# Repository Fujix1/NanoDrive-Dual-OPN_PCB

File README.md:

# NanoDrive-Dual-OPN_PCB
PCB of NanoDrive Dual OPN for KiCad 7.

<br />この 作品 は <a rel="license" href="http://creativecommons.org/licenses/by-nc-sa/4.0/">クリエイティブ・コモンズ 表示 - 非営利 - 継承 4.0 国際 ライセンス</a>の下に提供されています。

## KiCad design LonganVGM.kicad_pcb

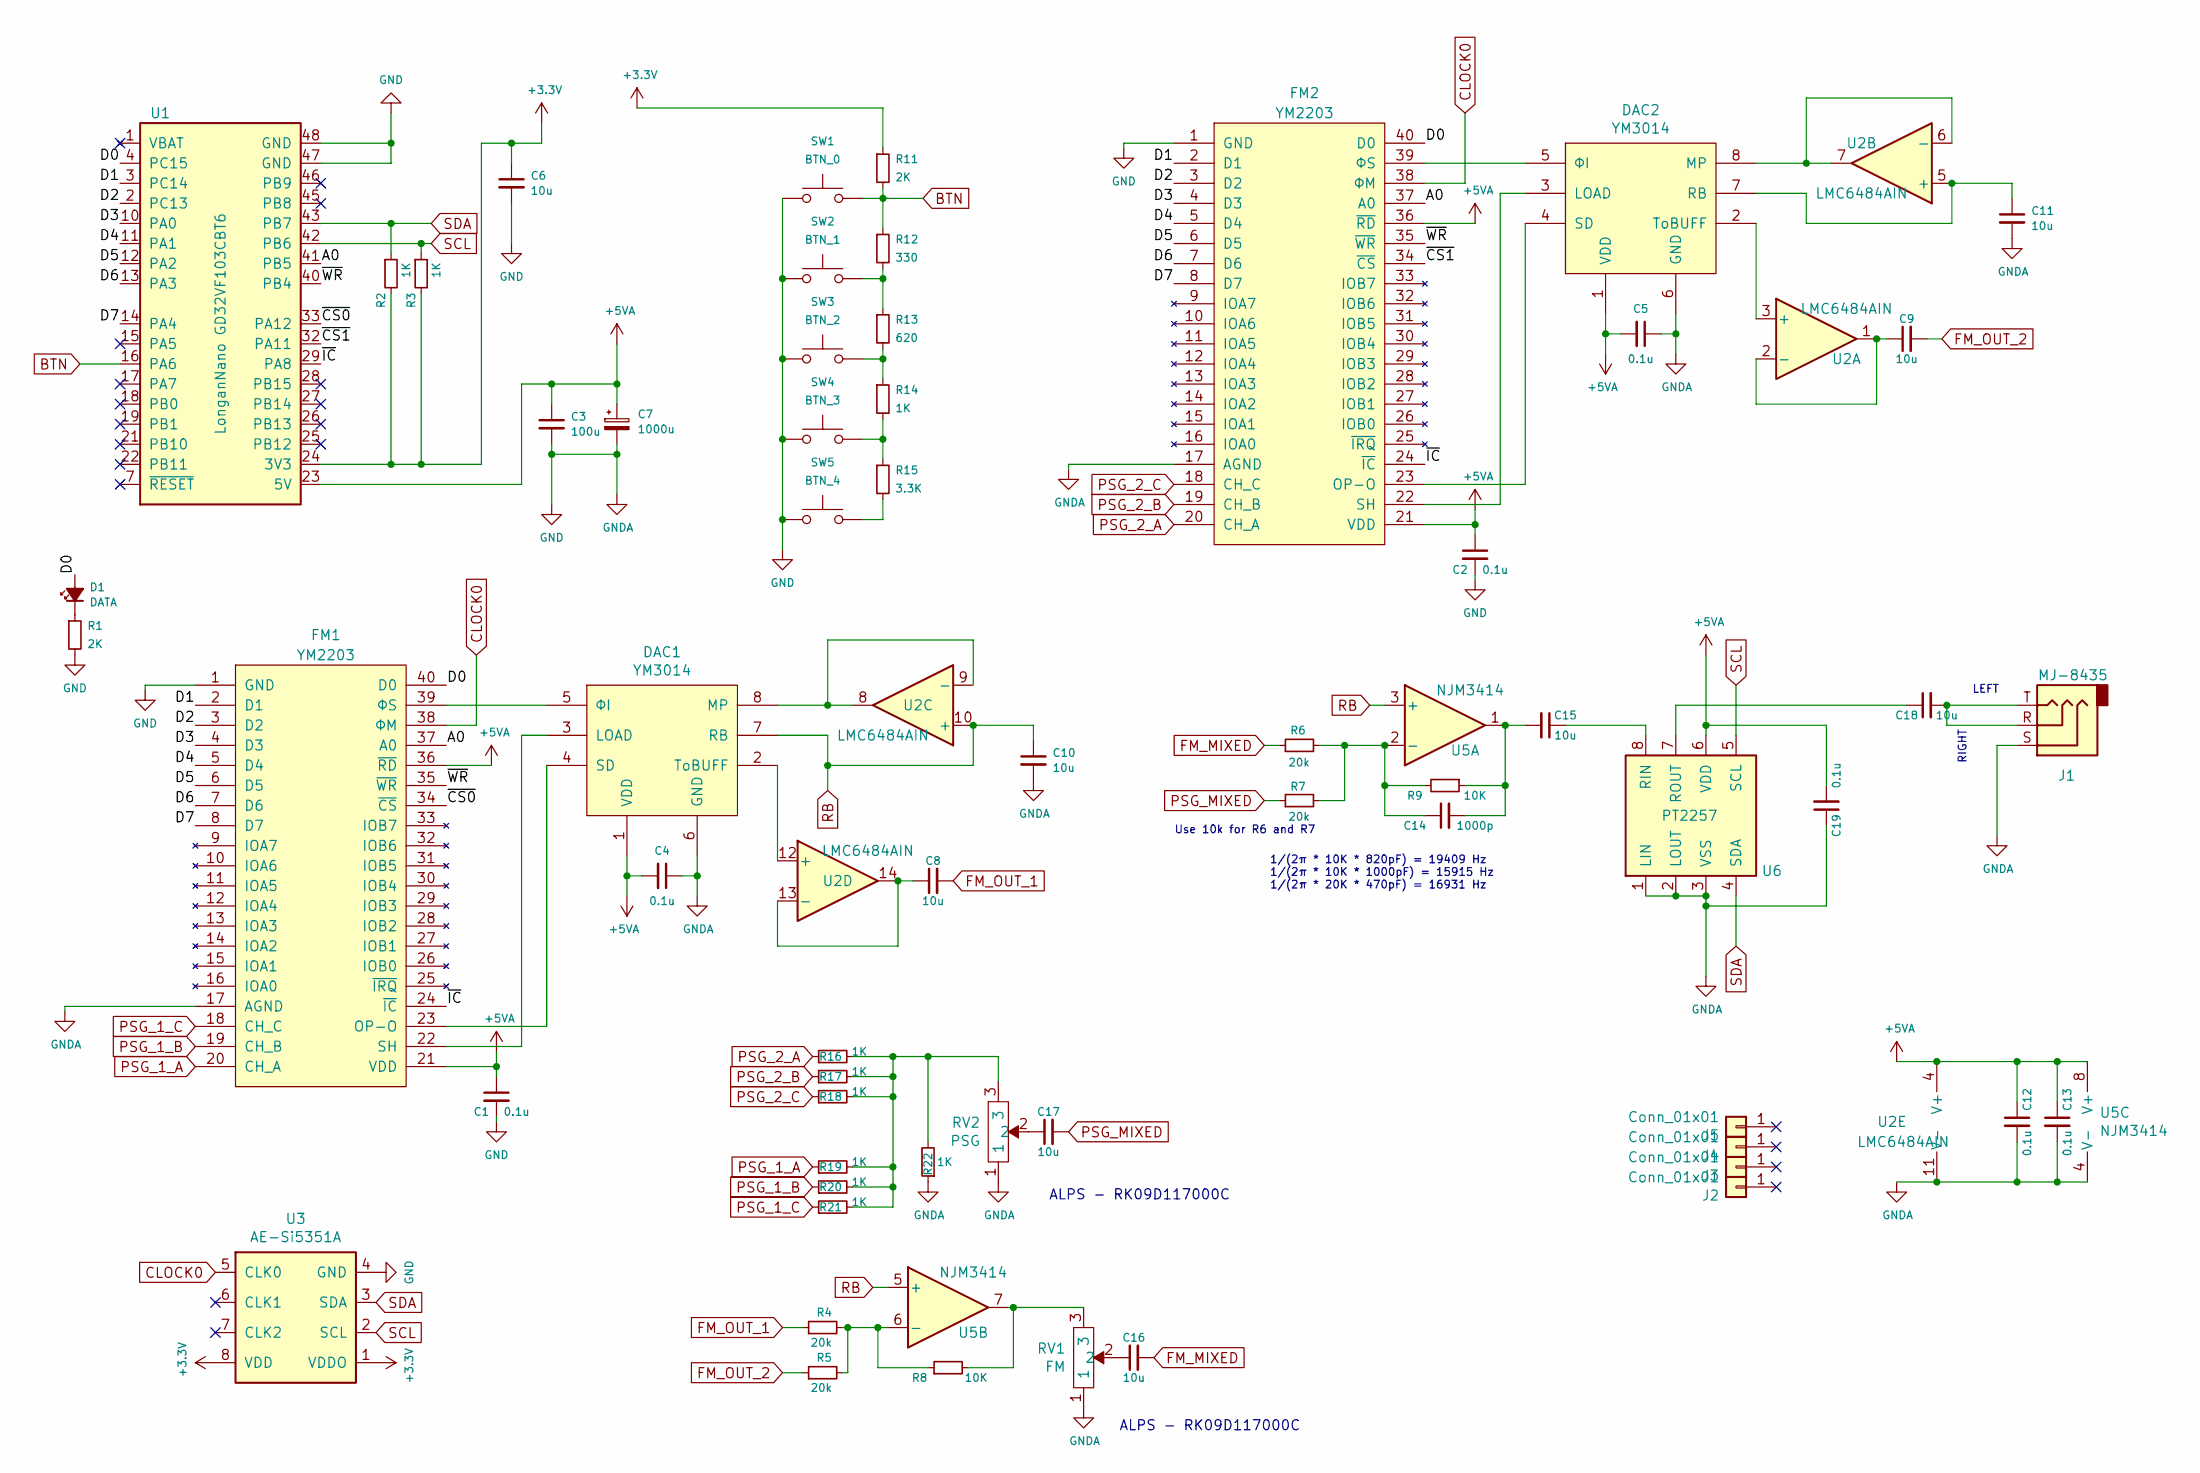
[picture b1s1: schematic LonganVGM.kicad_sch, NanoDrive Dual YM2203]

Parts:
C1, C2, C4, C5, C12, C13, C19: 0.1u; C_Disc_D4.3mm_W1.9mm_P5.00mm
C3: 100u; CP_Radial_D6.3mm_P2.50mm
C6, C8, C9, C10, C11, C15, C16, C17, C18: 10u; CP_Radial_D5.0mm_P2.00mm
C7: 1000u; CP_Radial_D8.0mm_P3.50mm
C14: 1000p; C_Disc_D4.3mm_W1.9mm_P5.00mm
D1: DATA; LED_D5.0mm_Clear
DAC1, DAC2: YM3014; DIP-8_W7.62mm_Socket
FM1, FM2: YM2203; DIP-40_W15.24mm_Socket
J1: MJ-8435; MJ8435
J2, J3, J4, J5: Conn_01x01; hole
R1, R11: 2K; R_Axial_DIN0207_L6.3mm_D2.5mm_P7.62mm_Horizontal
R2, R3, R14, R16, R17, R18, R19, R20, R21, R22: 1K; R_Axial_DIN0207_L6.3mm_D2.5mm_P7.62mm_Horizontal
R4, R5, R6, R7: 20k; R_Axial_DIN0207_L6.3mm_D2.5mm_P7.62mm_Horizontal
R8, R9: 10K; R_Axial_DIN0207_L6.3mm_D2.5mm_P7.62mm_Horizontal
R12: 330; R_Axial_DIN0207_L6.3mm_D2.5mm_P7.62mm_Horizontal
R13: 620; R_Axial_DIN0207_L6.3mm_D2.5mm_P7.62mm_Horizontal
R15: 3.3K; R_Axial_DIN0207_L6.3mm_D2.5mm_P7.62mm_Horizontal
RV1: FM; RK09D
RV2: PSG; RK09D
SW1: BTN_0; SW_PUSH_6mm_H4.3mm
SW2: BTN_1; SW_PUSH_6mm_H4.3mm
SW3: BTN_2; SW_PUSH_6mm_H4.3mm
SW4: BTN_3; SW_PUSH_6mm_H4.3mm
SW5: BTN_4; SW_PUSH_6mm_H4.3mm
U1: LonganNano GD32VF103CBT6; LonganNano
U2: LMC6484AIN; DIP-14_W7.62mm_Socket
U3: AE-Si5351A; DIP-8_W7.62mm_Socket
U5: NJM3414; DIP-8_W7.62mm_Socket
U6: PT2257; DIP-8_W7.62mm_Socket

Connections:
+3V3: C6.1, R2.2, R3.2, R11.1, U1.24 (3V3), U3.1 (VDDO), U3.8 (VDD)
+5VA: C1.1, C2.1, C3.1, C4.2, C5.2, C7.1, C12.1, C13.1, C19.2, DAC1.1 (VDD), DAC2.1 (VDD), FM1.21 (VDD), FM1.36 (~RD), FM2.21 (VDD), FM2.36 (~RD), U1.23 (5V), U2.4 (V+), U5.8 (V+), U6.6 (VDD)
/A0: FM1.37 (A0), FM2.37 (A0), U1.41 (PB5)
/D0: D1.2 (A), FM1.40 (D0), FM2.40 (D0), U1.4 (PC15)
/D1: FM1.2 (D1), FM2.2 (D1), U1.3 (PC14)
/D2: FM1.3 (D2), FM2.3 (D2), U1.2 (PC13)
/D3: FM1.4 (D3), FM2.4 (D3), U1.10 (PA0)
/D4: FM1.5 (D4), FM2.5 (D4), U1.11 (PA1)
/D5: FM1.6 (D5), FM2.6 (D5), U1.12 (PA2)
/D6: FM1.7 (D6), FM2.7 (D6), U1.13 (PA3)
/D7: FM1.8 (D7), FM2.8 (D7), U1.14 (PA4)
/~CS0: FM1.34 (~CS), U1.33 (PA12)
/~CS1: FM2.34 (~CS), U1.32 (PA11)
/~IC: FM1.24 (~IC), FM2.24 (~IC), U1.29 (PA8)
/~WR: FM1.35 (~WR), FM2.35 (~WR), U1.40 (PB4)
BTN: R11.2, R12.1, SW1.2, U1.16 (PA6)
CLOCK0: FM1.38 (ΦM), FM2.38 (ΦM), U3.5 (CLK0)
FM_MIXED: C16.2, R6.1
FM_OUT_1: C8.2, R4.1
FM_OUT_2: C9.2, R5.1
GND: C1.2, C2.2, C3.2, C4.1, C5.1, C6.2, C7.2, C10.2, C11.2, C12.2, C13.2, C19.1, DAC1.6 (GND), DAC2.6 (GND), FM1.1 (GND), FM1.17 (AGND), FM2.1 (GND), FM2.17 (AGND), J1.S, R1.2, R22.1, RV1.1, RV2.1, SW1.1, SW2.1, SW3.1, SW4.1, SW5.1, U1.47 (GND), U1.48 (GND), U2.11 (V-), U3.4 (GND), U5.4 (V-), U6.1 (LIN), U6.2 (LOUT), U6.3 (VSS)
unnamed: C8.1, U2.13 (-), U2.14
unnamed: C9.1, U2.1, U2.2 (-)
unnamed: C11.1, DAC2.7 (RB), U2.5 (+)
unnamed: C14.1, R6.2, R7.2, R9.2, U5.2 (-)
unnamed: C14.2, C15.2, R9.1, U5.1
unnamed: C15.1, U6.8 (RIN)
unnamed: C16.1, RV1.2
unnamed: C17.1, RV2.2
unnamed: C18.1, U6.7 (ROUT)
unnamed: C18.2, J1.R, J1.T
unnamed: D1.1 (K), R1.1
unnamed: DAC1.2 (ToBUFF), U2.12 (+)
unnamed: DAC1.3 (LOAD), FM1.22 (SH)
unnamed: DAC1.4 (SD), FM1.23 (OP-O)
unnamed: DAC1.5 (ΦI), FM1.39 (ΦS)
unnamed: DAC1.8 (MP), U2.8, U2.9 (-)
unnamed: DAC2.2 (ToBUFF), U2.3 (+)
unnamed: DAC2.3 (LOAD), FM2.22 (SH)
unnamed: DAC2.4 (SD), FM2.23 (OP-O)
unnamed: DAC2.5 (ΦI), FM2.39 (ΦS)
unnamed: DAC2.8 (MP), U2.6 (-), U2.7
unnamed: R4.2, R5.2, R8.1, U5.6 (-)
unnamed: R8.2, RV1.3, U5.7
unnamed: R12.2, R13.1, SW2.2
unnamed: R13.2, R14.1, SW3.2
unnamed: R14.2, R15.1, SW4.2
unnamed: R15.2, SW5.2
unnamed: R16.2, R17.2, R18.2, R19.2, R20.2, R21.2, R22.2, RV2.3
PSG_1_A: FM1.20 (CH_A), R19.1
PSG_1_B: FM1.19 (CH_B), R20.1
PSG_1_C: FM1.18 (CH_C), R21.1
PSG_2_A: FM2.20 (CH_A), R16.1
PSG_2_B: FM2.19 (CH_B), R17.1
PSG_2_C: FM2.18 (CH_C), R18.1
PSG_MIXED: C17.2, R7.1
RB: C10.1, DAC1.7 (RB), U2.10 (+), U5.3 (+), U5.5 (+)
SCL: R3.1, U1.42 (PB6), U3.2 (SCL), U6.5 (SCL)
SDA: R2.1, U1.43 (PB7), U3.3 (SDA), U6.4 (SDA)

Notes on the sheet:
ALPS - RK09D117000C
LEFT
1/(2π * 10K * 820pF) = 19409 Hz 1/(2π * 10K * 1000pF) = 15915 Hz 1/(2π * 20K * 470pF) = 16931 Hz
Use 10k for R6 and R7
RIGHT

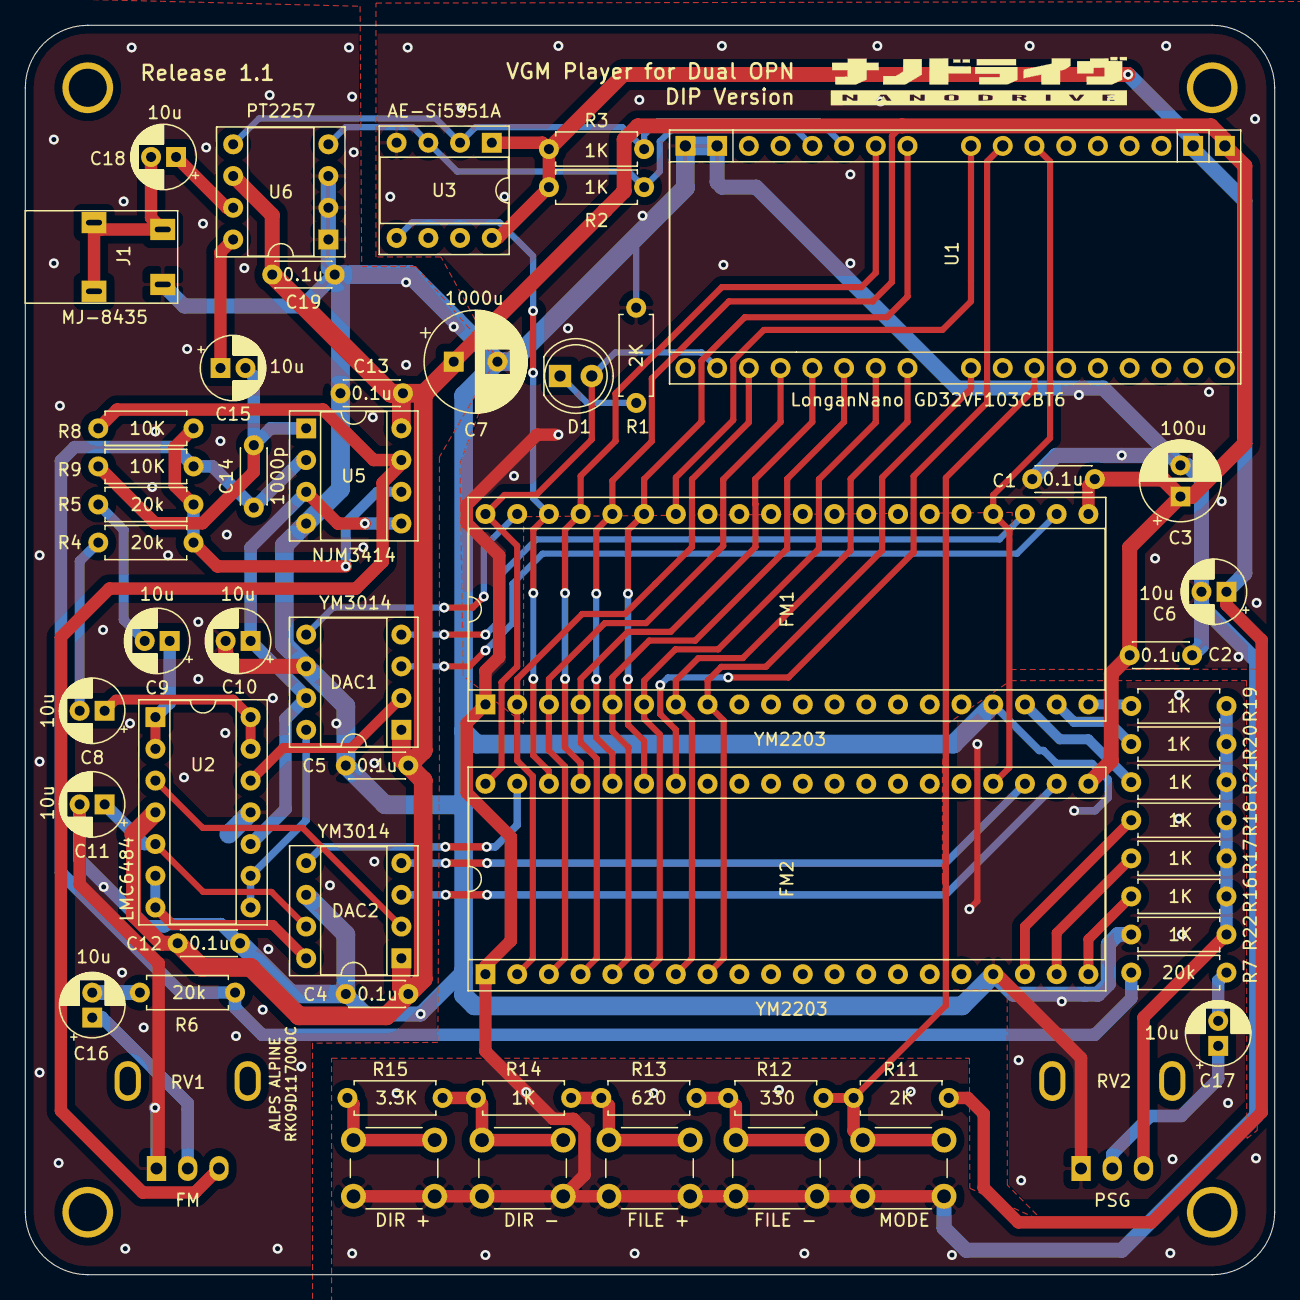
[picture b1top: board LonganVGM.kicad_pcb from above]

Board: 2 copper layers, 100.0 x 100.0 mm, 62 parts (0 on the bottom side), 59 nets.

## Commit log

2023-03-27 init
2023-03-27 LICENSE

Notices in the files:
README.md:
CC BY-NC-SA 4.0
